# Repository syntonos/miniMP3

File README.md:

# miniMP3

## About
A compact music player. 59.3 x 32 x 27 (mm), or around 2 x 1 x 1 inches, around half the size of an earpod case. Bluetooth and 3.5mm jack compatible. mp3, wav, and flac compatible. 5-band EQ, and more functions when the firmware updates. 

Really more of a fun PCB tiling exercise than anything. 

## Assembly
Solder on:
- the display module
    - Make sure the alignment is correct! Orient the screen upwards and covering the "blank" side of the PCB. Check the pins to make sure they match. Solder in the pins. Clip off the excess length.
    
- the SD card module
    - Orient the slot facing outwards. Make sure the pins match on the module and the PCB. Make sure the length of the header pin is appropriate (5mm). Solder in the pins. Clip off the excess length. 
    
    (throughhole slots below where the module is pictured)
- the boot switch (4x4 push switch)
    - Surface mount on the back. Make sure the orientation is correct (longer side matches the longer side, the shorter side matches the shorter side), then use solder paste and carefully place.
    
    (exposed solder pads next to the ESP32-WROOM-32)
- the power switch (toggle switch)
    - Orient so that the pins align (no specific direction), then solder in the throughhole pins.
    
    (bottom right corner)
- the rotary switches
    - Next to the OLED display module on the same side. Use solder paste to adhere the switches through a surface mount.
    
    (right side, two switches)

Plug in the LiPo Battery (JST-PH 2.0mm).

Insert the heat-sets into the two slots above and below. 

Fasten in the M2 screw on the bottom. 

## Firmware

Flash firmware through USB-C, and a platform like Arduino IDE. Hold the boot button, flick the power switch on and off, select the right USB connection, and upload the firmware.

(Firmware currently in testing, will be in release notes when fully finished.)

## PCB
### Layer 1 - Signal

### Layer 2 - GND

### Layer 3 - Power

### Layer 4 - Signal

### 3D Model Front

### 3D Model Back

## Schematic
 
## CAD

## BOM (List)
- 1x PCB 
- 1x SD Card Module
- 1x 1.54" OLED Display Module
- 1x PJ320-D Jack
- 1x 4mmx4mm Push Switch
- 1x Sliding Power Switch
- 2x Rotary Switch XUNPU
- 2x M2 Heatset 3.5D 4.5H
- 2x M2 Heatset 3.5D 18H
- 2x M2 Screw 20H 
- 1x 1000 mAh 102050 LiPo 

## BOM (Expanded)

- 1x PCB 
    - $118.54 + variable shipping + tariffs ([JLCPCB](jlcpcb.com)) 
- 1x SD Card Module
    - $2.22 ([Aliexpress](https://www.aliexpress.us/item/3256810092532833.html?spm=a2g0o.detail.pcDetailBottomMoreOtherSeller.20.4a9c4827KucpTU&gps-id=pcDetailBottomMoreOtherSeller&scm=1007.40050.354490.0&scm_id=1007.40050.354490.0&scm-url=1007.40050.354490.0&pvid=48008c8b-14f3-4bec-a2a7-858a0f19360f&_t=gps-id%3ApcDetailBottomMoreOtherSeller%2Cscm-url%3A1007.40050.354490.0%2Cpvid%3A48008c8b-14f3-4bec-a2a7-858a0f19360f%2Ctpp_buckets%3A668%232846%238113%231998&pdp_ext_f=%7B%22order%22%3A%22502%22%2C%22eval%22%3A%221%22%2C%22sceneId%22%3A%2230050%22%2C%22fromPage%22%3A%22recommend%22%7D&pdp_npi=6%40dis%21USD%212.22%211.11%21%21%2114.87%217.43%21%402101ea8f17861045160773710e0f03%2112000051759912175%21rec%21US%21%21ABX%211%210%21n_tag%3A-29910%3Bd%3A32a296a5%3Bm03_new_user%3A-29895&utparam-url=scene%3ApcDetailBottomMoreOtherSeller%7Cquery_from%3A%7Cx_object_id%3A1005010278847585%7C_p_origin_prod%3A))
- 1x 1.54" OLED Display Module
    - $5.01 ([Aliexpress](https://www.aliexpress.us/item/3256807368835856.html?spm=a2g0o.productlist.main.2.7ff4pLmCpLmCYY&algo_pvid=83d0ca85-7b2b-4d53-a13f-587b26adf1f2&pdp_ext_f=%7B%22order%22%3A%22134%22%2C%22eval%22%3A%221%22%2C%22fromPage%22%3A%22search%22%7D&utparam-url=scene%3Asearch%7Cquery_from%3A%7Cx_object_id%3A1005007555150608%7C_p_origin_prod%3A&gatewayAdapt=glo2usa4itemAdapt#nav-specification))
- 1x PJ320-D Jack
    - $1.29 ([Aliexpress](https://www.aliexpress.us/item/2255800475593383.html?spm=a2g0o.productlist.main.5.7a37165c4wg8d5&algo_pvid=d4e30b7e-5e70-4b23-910d-9174d61dcc92&algo_exp_id=d4e30b7e-5e70-4b23-910d-9174d61dcc92-4&pdp_ext_f=%7B%22order%22%3A%22280%22%2C%22eval%22%3A%221%22%2C%22fromPage%22%3A%22search%22%7D&pdp_npi=6%40dis%21USD%211.29%210.99%21%21%211.29%210.99%21%402103094f17861049205907001e0e9b%2110000005519439913%21sea%21US%210%21ABX%211%210%21n_tag%3A-29910%3Bd%3A3c5a3cb9%3Bm03_new_user%3A-29895%3BpisId%3A5000000210792324&curPageLogUid=lgUlXJGyB23m&utparam-url=scene%3Asearch%7Cquery_from%3A%7Cx_object_id%3A4000661908135%7C_p_origin_prod%3A))
- 1x 4mmx4mm Push Switch
    - $4.70 ([Aliexpress](https://www.aliexpress.us/item/3256812363662693.html?spm=a2g0o.productlist.main.2.9f2afc6hfc6hgc&algo_pvid=ce5fb20e-1501-429b-bf35-2a32c0622efe&algo_exp_id=ce5fb20e-1501-429b-bf35-2a32c0622efe-1&pdp_ext_f=%7B%22order%22%3A%2215%22%2C%22eval%22%3A%221%22%2C%22fromPage%22%3A%22search%22%7D&pdp_npi=6%40dis%21USD%214.37%210.99%21%21%2129.36%216.66%21%402101e81117861057478814823e0e95%2112000058673759179%21sea%21US%210%21ABX%211%210%21n_tag%3A-29910%3Bd%3Abf24fdfb%3Bm03_new_user%3A-29895%3BpisId%3A5000000210792324&curPageLogUid=IB3bPPIi35gd&utparam-url=scene%3Asearch%7Cquery_from%3A%7Cx_object_id%3A1005012549977445%7C_p_origin_prod%3A))
- 1x Sliding Power Switch
    - $3.18 ([Aliexpress](https://www.aliexpress.us/item/3256809238668355.html?spm=a2g0o.productlist.main.5.73ee3b50pr4ynz&algo_pvid=e15007de-cf57-41c3-bf81-98b1eed3ce96&algo_exp_id=e15007de-cf57-41c3-bf81-98b1eed3ce96-4&pdp_ext_f=%7B%22order%22%3A%2213%22%2C%22eval%22%3A%221%22%2C%22fromPage%22%3A%22search%22%7D&pdp_npi=6%40dis%21USD%213.18%210.99%21%21%213.18%210.99%21%40210328c017861059128021204e0db7%2112000049056299795%21sea%21US%210%21ABX%211%210%21n_tag%3A-29910%3Bd%3Abf24fdfb%3Bm03_new_user%3A-29895%3BpisId%3A5000000210792324&curPageLogUid=Vd35dkvN3lM2&utparam-url=scene%3Asearch%7Cquery_from%3A%7Cx_object_id%3A1005009424983107%7C_p_origin_prod%3A))
- 2x Rotary Switch XUNPU
    - $4.83 ([Aliexpress](https://www.aliexpress.us/item/3256806896633044.html?spm=a2g0o.productlist.main.3.451215b2cE25ay&algo_pvid=7b264ad5-283b-484e-a52d-678e4ecfdac7&algo_exp_id=7b264ad5-283b-484e-a52d-678e4ecfdac7-2&pdp_ext_f=%7B%22order%22%3A%224%22%2C%22eval%22%3A%221%22%2C%22fromPage%22%3A%22search%22%7D&pdp_npi=6%40dis%21USD%214.83%210.99%21%21%2132.44%216.69%21%4021032c8d17861060857714961e4bdc%2112000039340479749%21sea%21US%210%21ABX%211%210%21n_tag%3A-29910%3Bd%3Abf24fdfb%3Bm03_new_user%3A-29895%3BpisId%3A5000000210792324&curPageLogUid=fBZcXmDou4el&utparam-url=scene%3Asearch%7Cquery_from%3A%7Cx_object_id%3A1005007082947796%7C_p_origin_prod%3A))
- 2x M2 Heatset 3.5D 4.5H
    - $5.54 ([Aliexpress](https://www.aliexpress.us/item/3256806611972099.html?spm=a2g0o.productlist.main.4.258012795phy4k&aem_p4p_detail=202607030045232645786979741340002311817&algo_pvid=48fed4a3-d046-4065-9380-83ce295cbbc4&algo_exp_id=48fed4a3-d046-4065-9380-83ce295cbbc4-3&pdp_ext_f=%7B%22order%22%3A%223867%22%2C%22spu_best_type%22%3A%22price%22%2C%22eval%22%3A%221%22%2C%22fromPage%22%3A%22search%22%7D&pdp_npi=6%40dis%21TWD%21237.09%21189.65%21%21%2148.63%2138.90%21%400b1bf20a17830647230337253ec923%2112000038340344511%21sea%21TW%217611495303%21ABX%211%210%21n_tag%3A-29910%3Bd%3A8099445a%3Bm03_new_user%3A-29895&curPageLogUid=pmRS9OHkPpDI&utparam-url=scene%3Asearch%7Cquery_from%3A%7Cx_object_id%3A1005006798286851%7C_p_origin_prod%3A&search_p4p_id=202607030045232645786979741340002311817_1&gatewayAdapt=glo2usa4itemAdapt))
- 2x M2 Heatset 3.5D 18H
    - $8.00 ([Aliexpress](https://www.aliexpress.us/item/3256806611972099.html?spm=a2g0o.productlist.main.4.258012795phy4k&aem_p4p_detail=202607030045232645786979741340002311817&algo_pvid=48fed4a3-d046-4065-9380-83ce295cbbc4&algo_exp_id=48fed4a3-d046-4065-9380-83ce295cbbc4-3&pdp_ext_f=%7B%22order%22%3A%223867%22%2C%22spu_best_type%22%3A%22price%22%2C%22eval%22%3A%221%22%2C%22fromPage%22%3A%22search%22%7D&pdp_npi=6%40dis%21TWD%21237.09%21189.65%21%21%2148.63%2138.90%21%400b1bf20a17830647230337253ec923%2112000038340344511%21sea%21TW%217611495303%21ABX%211%210%21n_tag%3A-29910%3Bd%3A8099445a%3Bm03_new_user%3A-29895&curPageLogUid=pmRS9OHkPpDI&utparam-url=scene%3Asearch%7Cquery_from%3A%7Cx_object_id%3A1005006798286851%7C_p_origin_prod%3A&search_p4p_id=202607030045232645786979741340002311817_1&gatewayAdapt=glo2usa4itemAdapt))
- 2x M2 Screw 20H 
    - $3.86 ([Aliexpress](https://www.aliexpress.us/item/3256801577619187.html?spm=a2g0o.productlist.main.16.b7047f20Gvg4hM&aem_p4p_detail=202607030206362312824948692800002217653&algo_pvid=bb9c3ac2-a29e-44a3-bcaa-9b5e252f7fca&algo_exp_id=bb9c3ac2-a29e-44a3-bcaa-9b5e252f7fca-15&pdp_ext_f=%7B%22order%22%3A%222238%22%2C%22eval%22%3A%221%22%2C%22fromPage%22%3A%22search%22%7D&pdp_npi=6%40dis%21TWD%2122.81%2121.82%21%21%210.69%210.66%21%402140f54217830695966233289eecdc%2112000017472413080%21sea%21TW%210%21ABX%211%210%21n_tag%3A-29910%3Bd%3Aae87e3a4%3Bm03_new_user%3A-29895&curPageLogUid=MdcYnRM4XBCg&utparam-url=scene%3Asearch%7Cquery_from%3A%7Cx_object_id%3A1005001763933939%7C_p_origin_prod%3A&search_p4p_id=202607030206362312824948692800002217653_4&gatewayAdapt=glo2usa4itemAdapt))
- 1x 1000 mAh 102050 LiPo 
    - $9.54 ([Aliexpress](https://www.aliexpress.us/item/3256812631640799.html?spm=a2g0o.productlist.main.14.2795V6V3V6V3Ci&algo_pvid=47981000-d41c-4af4-80eb-60457e2c9e29&algo_exp_id=47981000-d41c-4af4-80eb-60457e2c9e29-13&pdp_ext_f=%7B%22order%22%3A%22-1%22%2C%22eval%22%3A%221%22%2C%22fromPage%22%3A%22search%22%7D&pdp_npi=6%40dis%21USD%219.57%214.69%21%21%2164.21%2131.46%21%402101e7a317861054336146098e0cfe%2112000059462118130%21sea%21US%210%21ABX%211%210%21n_tag%3A-29910%3Bd%3A3c5a3cb9%3Bm03_new_user%3A-29895&curPageLogUid=SGpK83WOjezf&utparam-url=scene%3Asearch%7Cquery_from%3A%7Cx_object_id%3A1005012817955551%7C_p_origin_prod%3A))

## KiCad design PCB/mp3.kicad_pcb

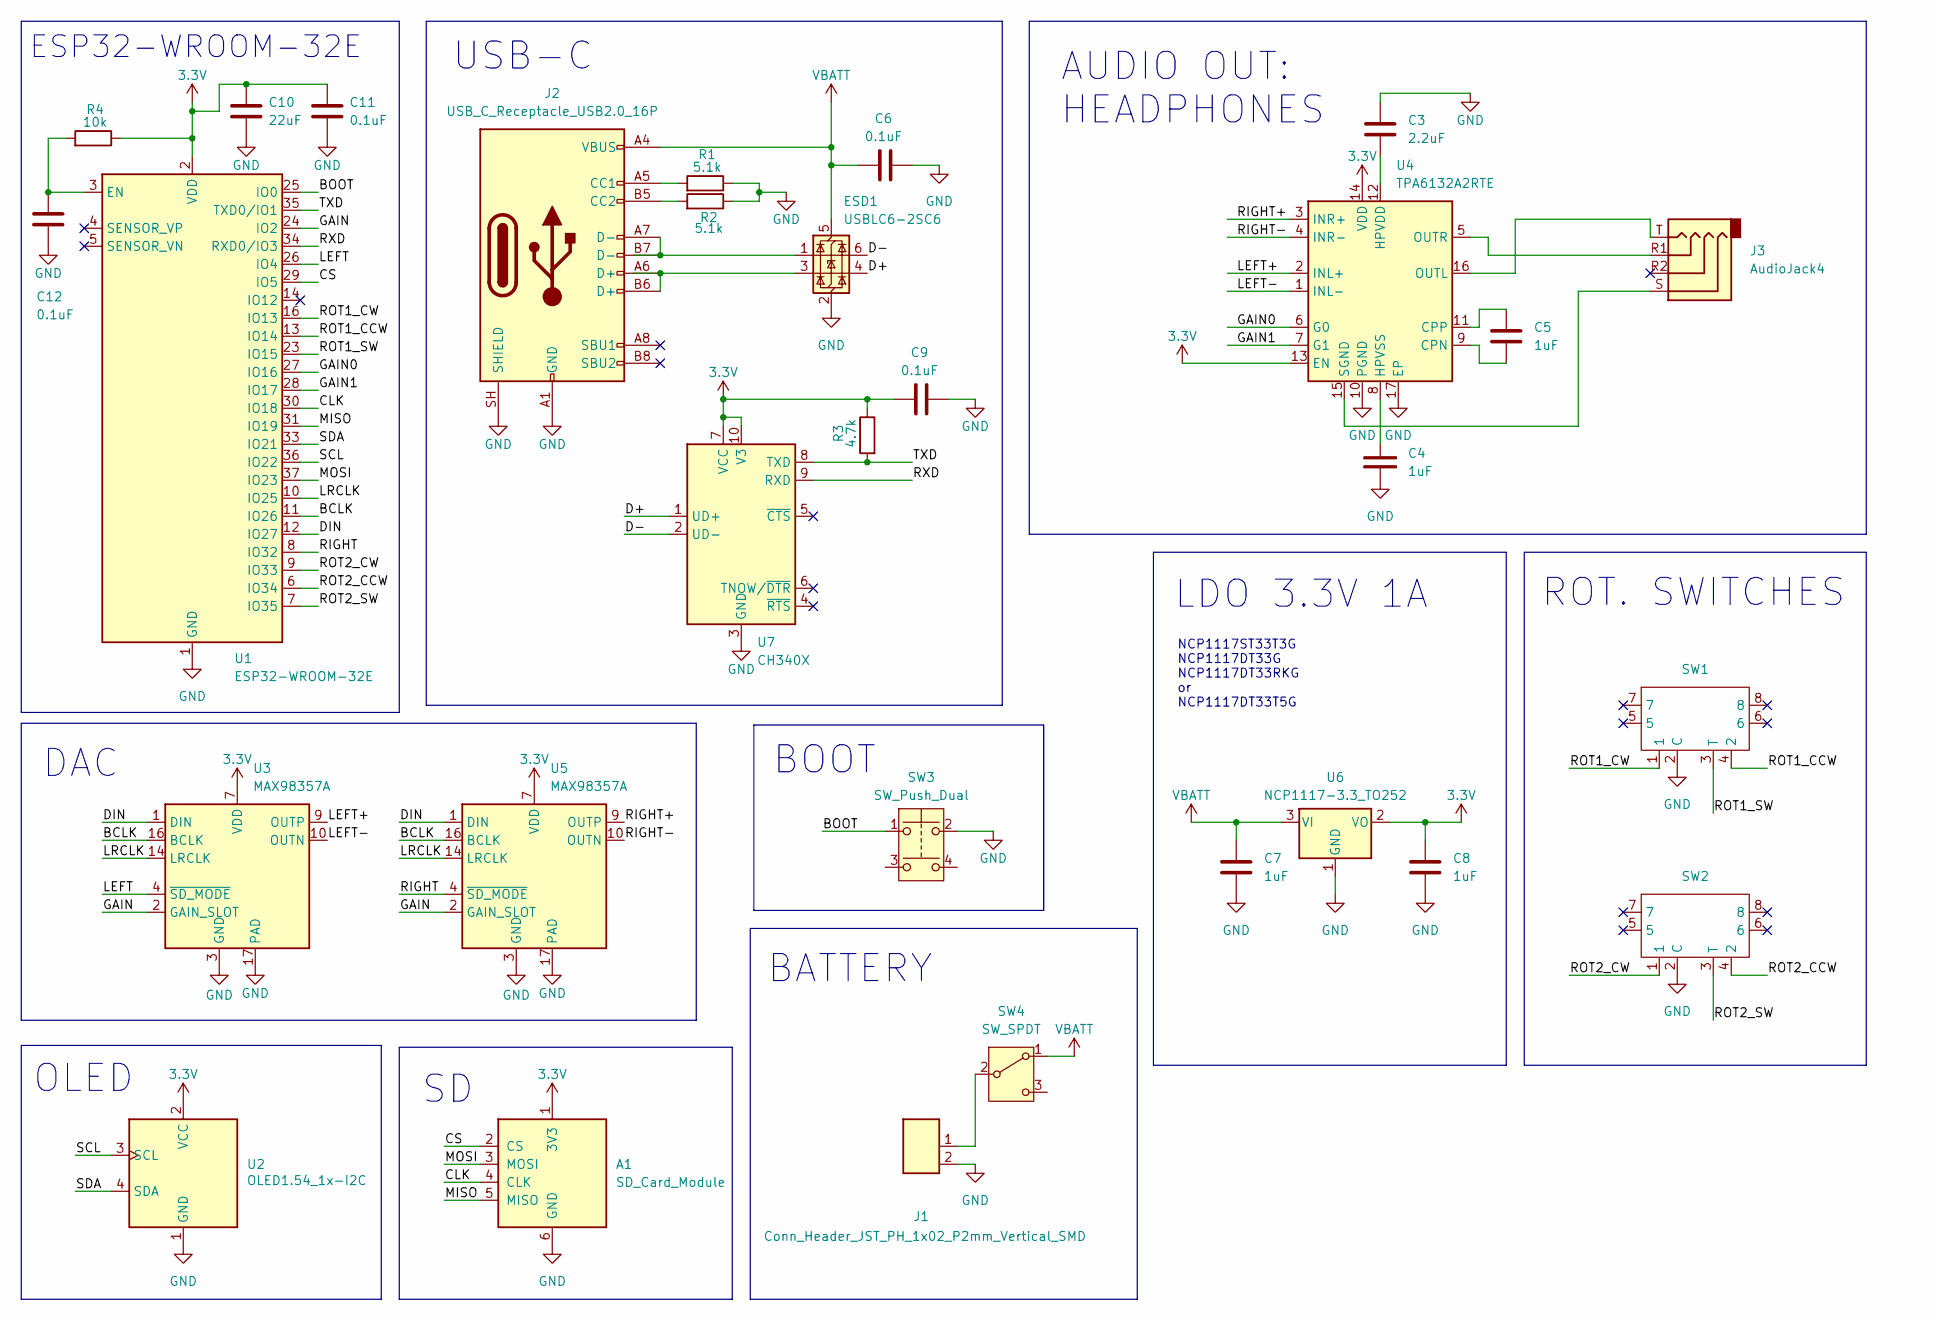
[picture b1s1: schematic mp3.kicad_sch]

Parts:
A1: SD_Card_Module
C3: 2.2uF; C_0603_1608Metric
C4, C5, C7, C8: 1uF; C_0603_1608Metric
C6, C9: 0.1uF; C_0603_1608Metric_Pad1.08x0.95mm_HandSolder
C10: 22uF; C_0603_1608Metric
C11, C12: 0.1uF; C_0603_1608Metric
ESD1: USBLC6-2SC6; SOT-23-6
J1: Conn_Header_JST_PH_1x02_P2mm_Vertical_SMD; Header_JST_PH_1x02_P2mm_Vertical_SMD
J2: USB_C_Receptacle_USB2.0_16P; USB-C_16
J3: AudioJack4; Jack_3.5mm_PJ320D_Horizontal_3D
R1, R2: 5.1k; R_0603_1608Metric
R3: 4.7k; R_0603_1608Metric
R4: 10k; R_0603_1608Metric
SW1, SW2: XUNPU QS-302-AGS8P
SW3: SW_Push_Dual; SW_Push_4x4mm
SW4: SW_SPDT; Untitled
U1: ESP32-WROOM-32E
U2: OLED1.54_1x-I2C; OLED 1.54in 4-pin Module
U3, U5: MAX98357A; TQFN-16-1EP_3x3mm_P0.5mm_EP1.23x1.23mm
U4: TPA6132A2RTE; WQFN-16-1EP_3x3mm_P0.5mm_EP1.6x1.6mm_ThermalVias
U6: NCP1117-3.3_TO252; TO-252-2
U7: CH340X; MSOP-10_3x3mm_P0.5mm

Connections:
3.3V: A1.1 (3V3), C8.1, C9.2, C10.1, C11.1, R3.2, R4.2, U1.2 (VDD), U2.2 (VCC), U3.7 (VDD), U3.8 (VDD), U4.13 (EN), U4.14 (VDD), U5.7 (VDD), U5.8 (VDD), U6.2 (VO), U7.7 (VCC), U7.10 (V3)
/BCLK: U1.11 (IO26), U3.16 (BCLK), U5.16 (BCLK)
/BOOT: SW3.1, U1.25 (IO0)
/CLK: A1.4 (CLK), U1.30 (IO18)
/CS: A1.2 (CS), U1.29 (IO5)
/D+: ESD1.4 (I/O2), U7.1 (UD+)
/D-: ESD1.6 (I/O1), U7.2 (UD-)
/DIN: U1.12 (IO27), U3.1 (DIN), U5.1 (DIN)
/GAIN: U1.24 (IO2), U3.2 (GAIN_SLOT), U5.2 (GAIN_SLOT)
/GAIN0: U1.27 (IO16), U4.6 (G0)
/GAIN1: U1.28 (IO17), U4.7 (G1)
/LEFT: U1.26 (IO4), U3.4 (~SD_MODE)
/LEFT+: U3.9 (OUTP), U4.2 (INL+)
/LEFT-: U3.10 (OUTN), U4.1 (INL-)
/LRCLK: U1.10 (IO25), U3.14 (LRCLK), U5.14 (LRCLK)
/MISO: A1.5 (MISO), U1.31 (IO19)
/MOSI: A1.3 (MOSI), U1.37 (IO23)
/RIGHT: U1.8 (IO32), U5.4 (~SD_MODE)
/RIGHT+: U4.3 (INR+), U5.9 (OUTP)
/RIGHT-: U4.4 (INR-), U5.10 (OUTN)
/ROT1_CCW: SW1.4 (2), U1.13 (IO14)
/ROT1_CW: SW1.1, U1.16 (IO13)
/ROT1_SW: SW1.3 (T), U1.23 (IO15)
/ROT2_CCW: SW2.4 (2), U1.6 (IO34)
/ROT2_CW: SW2.1, U1.9 (IO33)
/ROT2_SW: SW2.3 (T), U1.7 (IO35)
/RXD: U1.34 (RXD0/IO3), U7.9 (RXD)
/SCL: U1.36 (IO22), U2.3 (SCL)
/SDA: U1.33 (IO21), U2.4 (SDA)
/TXD: R3.1, U1.35 (TXD0/IO1), U7.8 (TXD)
GND: A1.6 (GND), C3.1, C4.1, C6.1, C7.2, C8.2, C9.1, C10.2, C11.2, C12.2, ESD1.2 (GND), J1.2, J2.A1 (GND), J2.A12 (GND), J2.B1 (GND), J2.B12 (GND), J2.GND, J2.SH (SHIELD), R1.2, R2.2, SW1.2 (C), SW2.2 (C), SW3.2, U1.1 (GND), U1.15 (GND), U1.38 (GND), U1.39 (GND), U2.1 (GND), U3.3 (GND), U3.11 (GND), U3.15 (GND), U3.17 (PAD), U4.10 (PGND), U4.17 (EP), U5.3 (GND), U5.11 (GND), U5.15 (GND), U5.17 (PAD), U6.1 (GND), U7.3 (GND)
unnamed: ESD1.1 (I/O1), J2.A7 (D-), J2.B7 (D-)
unnamed: ESD1.3 (I/O2), J2.A6 (D+), J2.B6 (D+)
unnamed: J2.A5 (CC1), R1.1
unnamed: J2.B5 (CC2), R2.1
unnamed: J1.1, SW4.2 (B)
unnamed: C12.1, R4.1, U1.3 (EN)
unnamed: C5.2, U4.9 (CPN)
unnamed: C5.1, U4.11 (CPP)
unnamed: C3.2, U4.12 (HPVDD)
unnamed: C4.2, U4.8 (HPVSS)
unnamed: J3.T, U4.16 (OUTL)
unnamed: J3.R1, U4.5 (OUTR)
unnamed: J3.S, U4.15 (SGND)
VBATT: C6.2, C7.1, ESD1.5 (VBUS), J2.A4 (VBUS), J2.A9 (VBUS), J2.B4 (VBUS), J2.B9 (VBUS), J2.VBUS, SW4.1 (A), U6.3 (VI)

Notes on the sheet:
DAC
NCP1117ST33T3G NCP1117DT33G NCP1117DT33RKG or NCP1117DT33T5G
ESP32-WROOM-32E
BATTERY
USB-C
LDO 3.3V 1A
OLED
BOOT
ROT. SWITCHES
AUDIO OUT: HEADPHONES

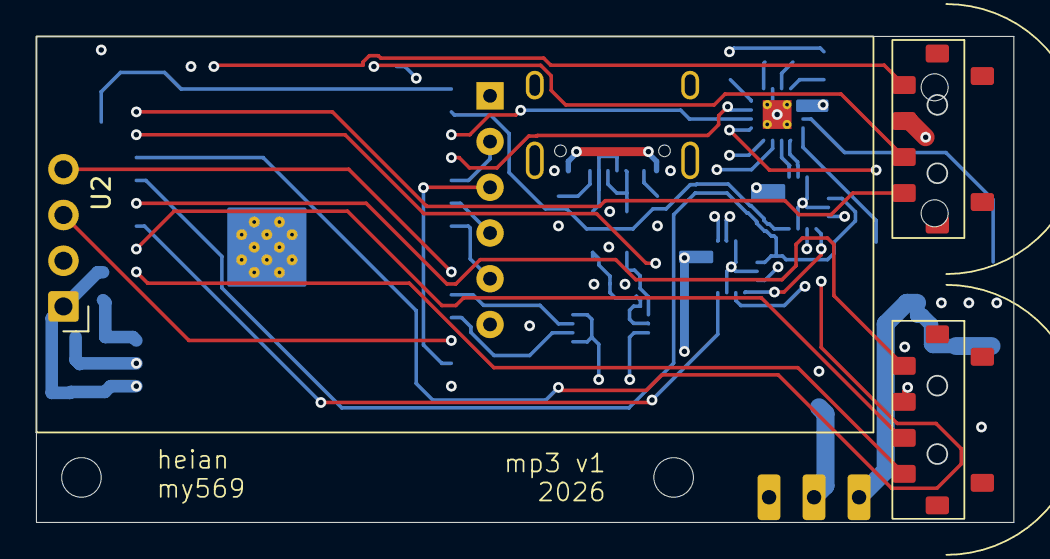
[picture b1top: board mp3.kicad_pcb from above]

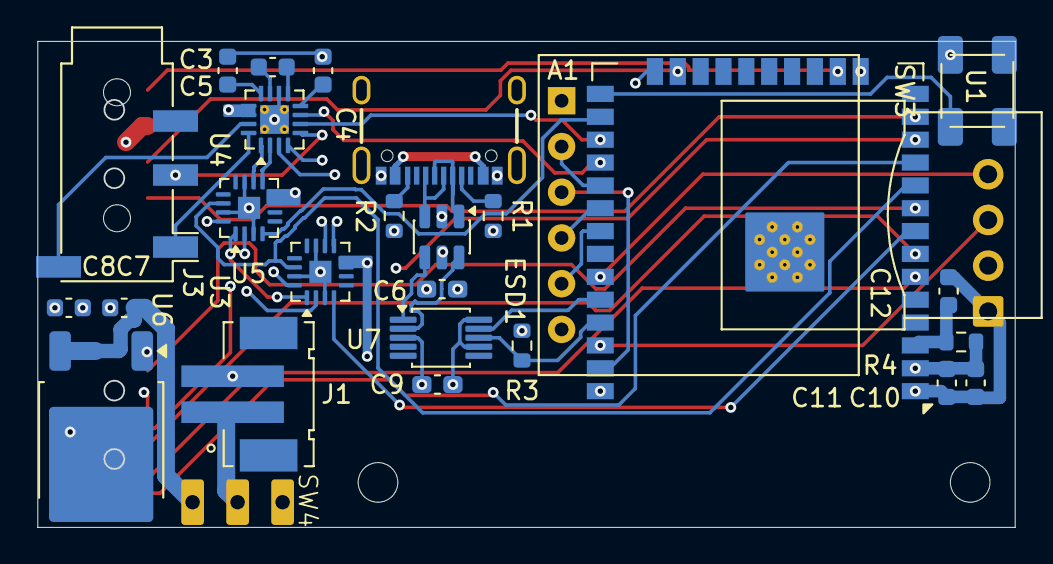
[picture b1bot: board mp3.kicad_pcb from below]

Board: 4 copper layers, 54.3 x 27.0 mm, 32 parts (27 on the bottom side), 45 nets.

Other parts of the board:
M1, M2: MountingHole_2.2mm_M2

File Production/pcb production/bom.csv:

Designator,Footprint,Quantity,Value,LCSC Part #
C10,0603,1,22uF,
"C11, C12, C6, C9",0603,4,0.1uF,
C3,0603,1,2.2uF,
"C4, C5, C7, C8",0603,4,1uF,
ESD1,SOT-23-6,1,USBLC6-2SC6,
J2,USB-C_16,1,USB_C_Receptacle_USB2.0_16P,
"R1, R2",0603,2,5.1k,
R3,0603,1,4.7k,
R4,0603,1,10k,
"SW1, SW2",XUNPU QS-302-AGS8P,2,~,
U1,ESP32-WROOM-32E,1,ESP32-WROOM-32E,
"U3, U5",TQFN-16-1EP_3x3mm_P0.5mm_EP1.23x1.23mm,2,MAX98357A,
U4,WQFN-16-1EP_3x3mm_P0.5mm_EP1.6x1.6mm_ThermalVias,1,TPA6132A2RTE,
U6,TO-252-2,1,NCP1117-3.3_TO252,
U7,MSOP-10_3x3mm_P0.5mm,1,CH340X,

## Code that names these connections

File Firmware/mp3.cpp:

//I2S
#define DIN 27
#define LRCLK 25
#define BCLK 26
#define LEFT 4
#define RIGHT 32
#define GAIN 2
#define GAIN0 16
#define GAIN1 17

//I2C
#define SDA 21
#define SCL 22

//SD (SPI)
#define CS 5
#define MOSI 23
#define MISO 19
#define CLK 18

//UART
#define TXD 1
#define RXD 3

//BOOT
#define BOOT 0  

//Rotary Encoder (MENU)
#define UP 14
#define DOWN 13
#define SELECT 15

//Rotary Encoder (VOLUME)
#define VOLUME_UP 34
#define VOLUME_DOWN 33
#define VOLUME_SELECT 35

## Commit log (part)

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2026-06-29 init commit
2026-06-29 readme + journal
